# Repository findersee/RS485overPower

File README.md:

# RS485overPower

RS-485 Over DC Powerline adapter

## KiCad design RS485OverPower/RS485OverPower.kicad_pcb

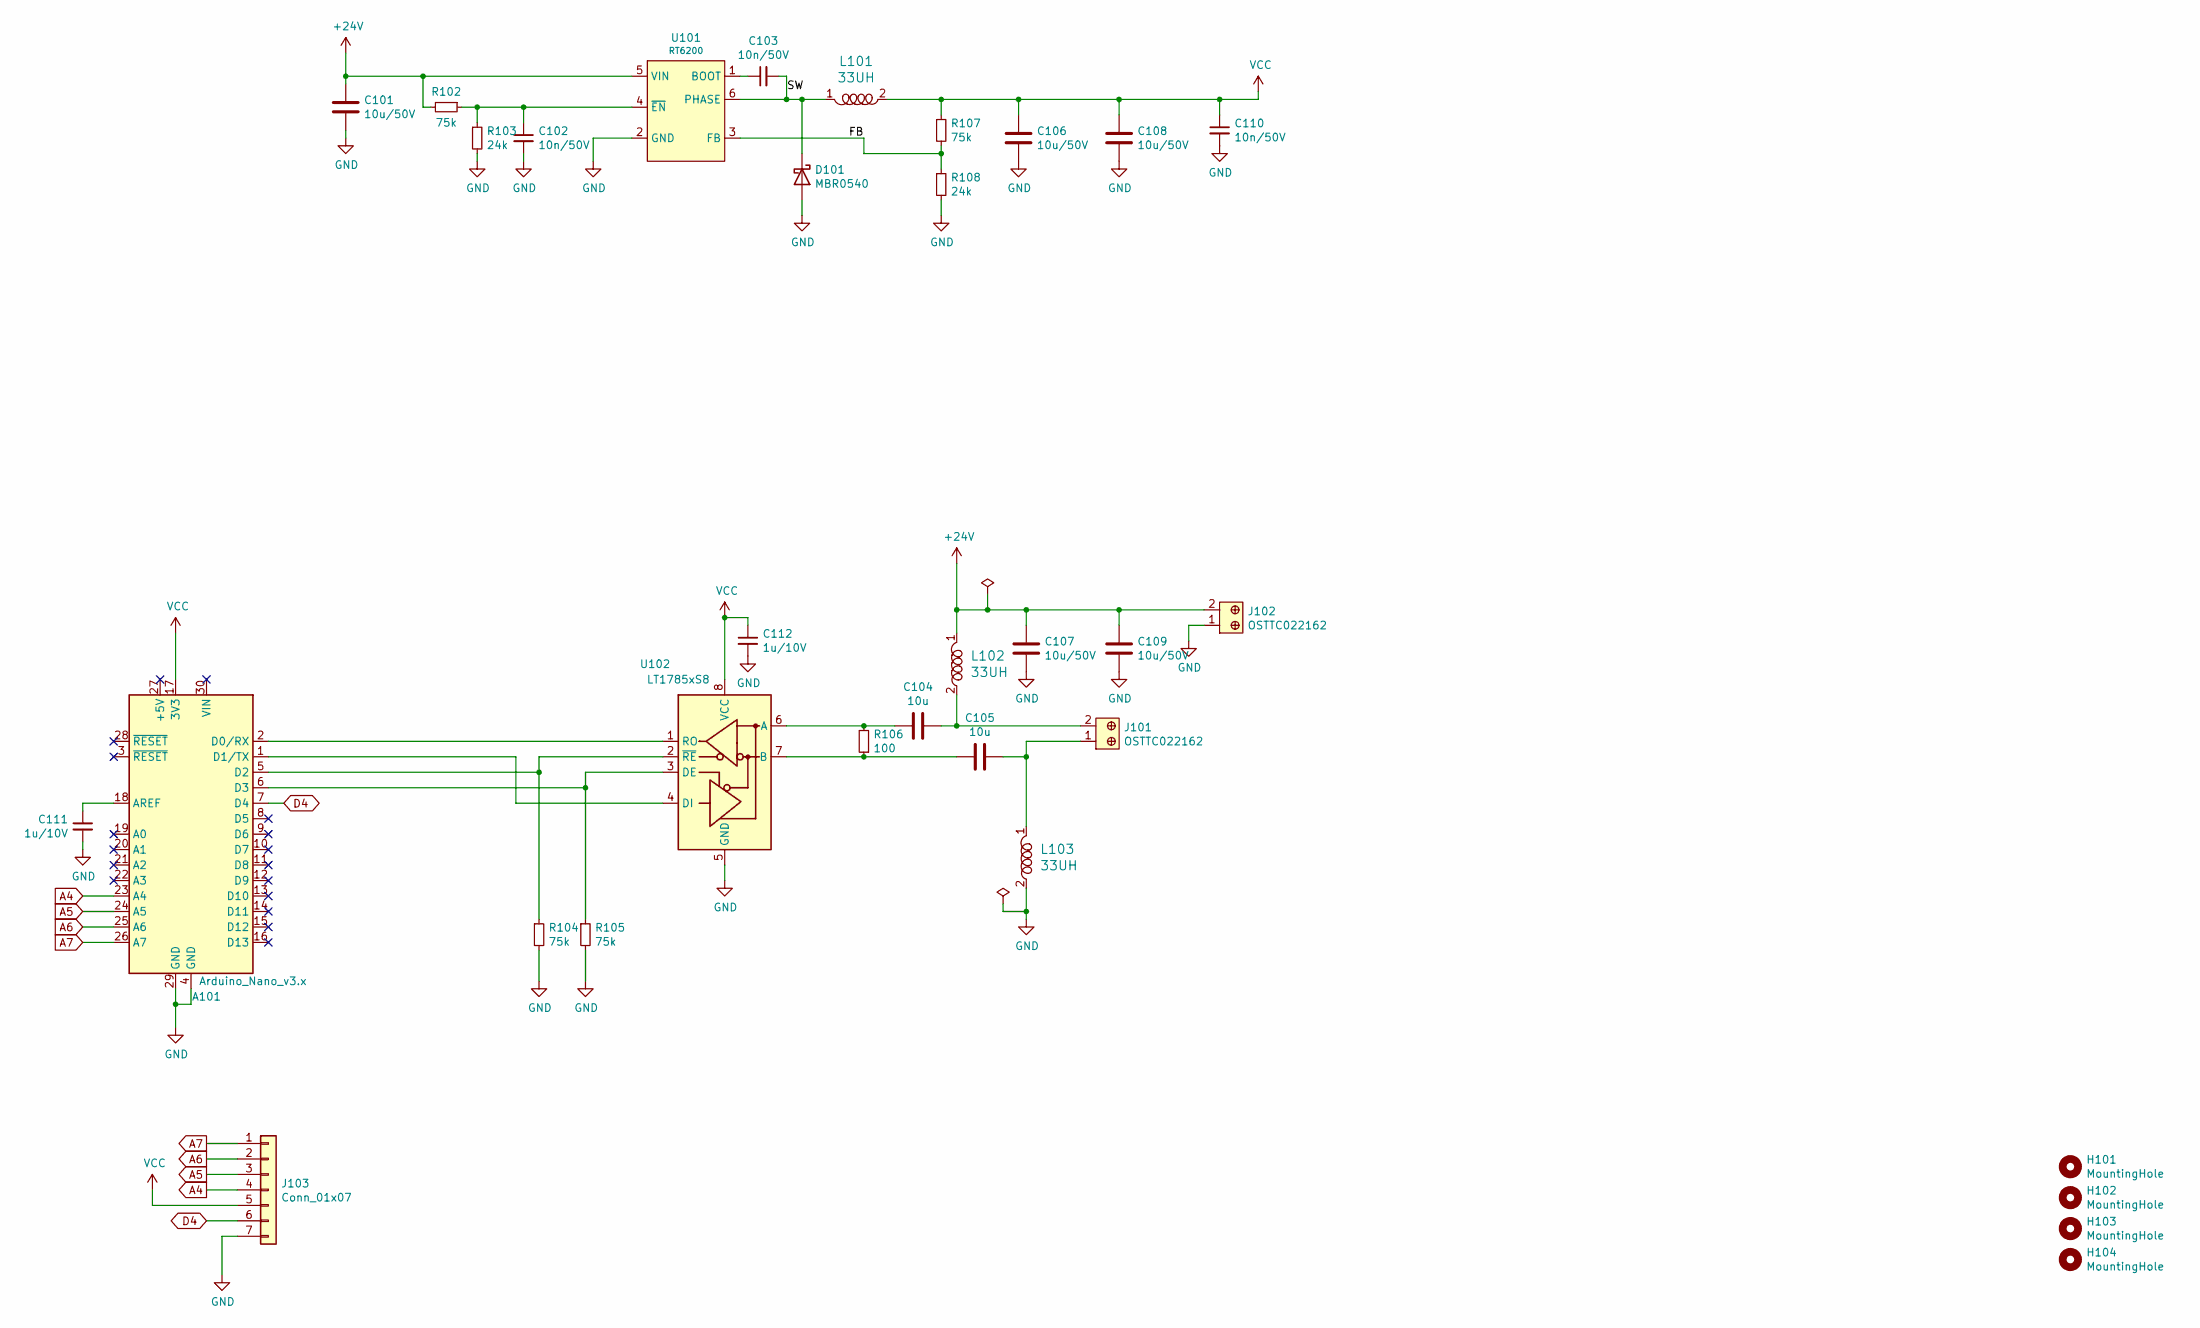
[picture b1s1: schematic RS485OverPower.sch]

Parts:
A101: Arduino_Nano_v3.x; Arduino_Nano
C101, C106, C107, C108: 10u/50V; C_0805_2012Metric
C102, C103, C110: 10n/50V; C_0603_1608Metric
C104, C105: 10u; C_0805_2012Metric
C109: 10u/50V; C_0603_1608Metric
C111, C112: 1u/10V; C_0603_1608Metric
D101: MBR0540; D_SOD-123
H101, H102, H103, H104: MountingHole; MountingHole_3.2mm_M3
J101, J102: OSTTC022162; Term_Block_1x2_P5.08MM; MPN OSTTC022162; Digi-Key_PN ED2609-ND
J103: Conn_01x07; PinHeader_1x07_P2.54mm_Vertical
L101, L102, L103: 33UH; MWSA0603; MPN MWSA0603-330MT; LCSC PN C132138
R102, R104, R105, R107: 75k; R_0603_1608Metric
R103, R108: 24k; R_0603_1608Metric
R106: 100; R_0603_1608Metric
U101: RT6200; SOT-23-6
U102: LT1785xS8; SOIC-8_3.9x4.9mm_P1.27mm

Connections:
+24V: C101.1, C107.1, C109.1, J102.2, L102.1, R102.2, U101.5 (VIN)
/FB: R107.2, R108.1, U101.3 (FB)
/SW: C103.2, D101.1 (K), L101.1, U101.6 (PHASE)
A4: A101.23 (A4), J103.4
A5: A101.24 (A5), J103.3
A6: A101.25 (A6), J103.2
A7: A101.26 (A7), J103.1
D4: A101.7 (D4), J103.6
GND: A101.4 (GND), A101.29 (GND), C101.2, C102.2, C106.2, C107.2, C108.2, C109.2, C110.2, C111.2, C112.2, D101.2 (A), J102.1, J103.7, L103.2, R103.2, R104.2, R105.2, R108.2, U101.2 (GND), U102.5 (GND)
unnamed: A101.1 (D1/TX), U102.4 (DI)
unnamed: A101.2 (D0/RX), U102.1 (RO)
unnamed: A101.5 (D2), R104.1, U102.2 (~RE)
unnamed: A101.6 (D3), R105.1, U102.3 (DE)
unnamed: A101.18 (AREF), C111.1
unnamed: C102.1, R102.1, R103.1, U101.4 (~EN)
unnamed: C103.1, U101.1 (BOOT)
unnamed: C104.1, J101.2, L102.2
unnamed: C104.2, R106.2, U102.6 (A)
unnamed: C105.1, R106.1, U102.7 (B)
unnamed: C105.2, J101.1, L103.1
VCC: A101.17 (3V3), C106.1, C108.1, C110.1, C112.1, J103.5, L101.2, R107.1, U102.8 (VCC)

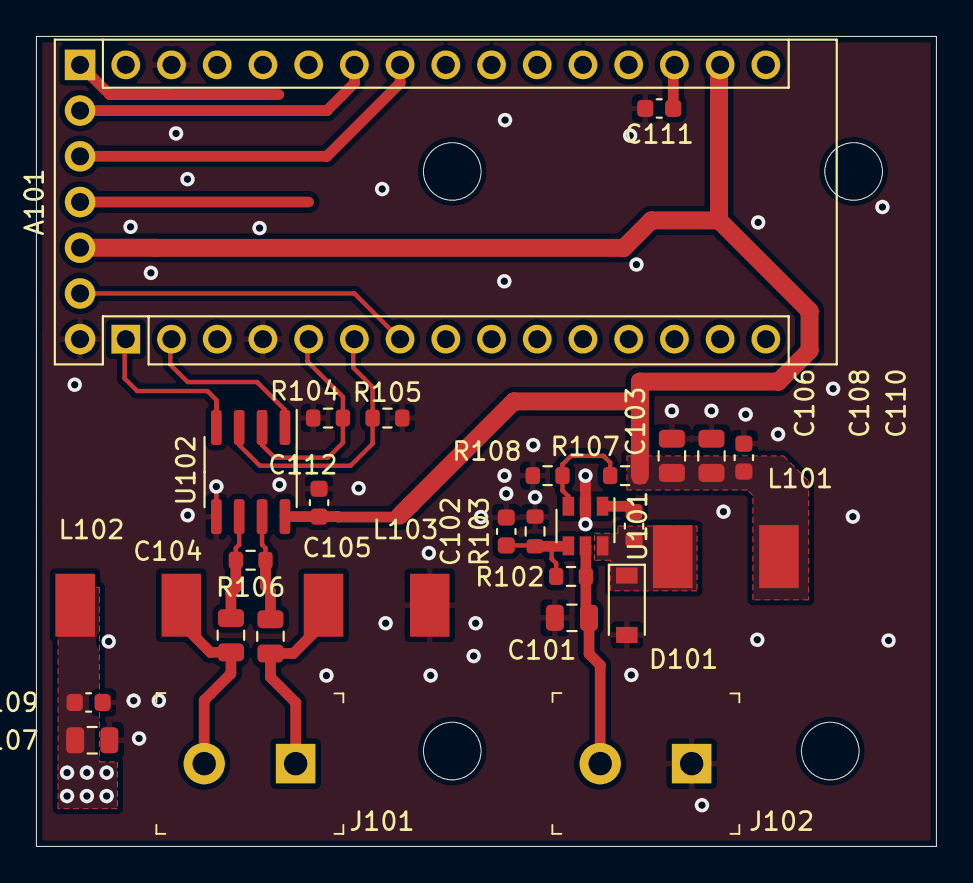
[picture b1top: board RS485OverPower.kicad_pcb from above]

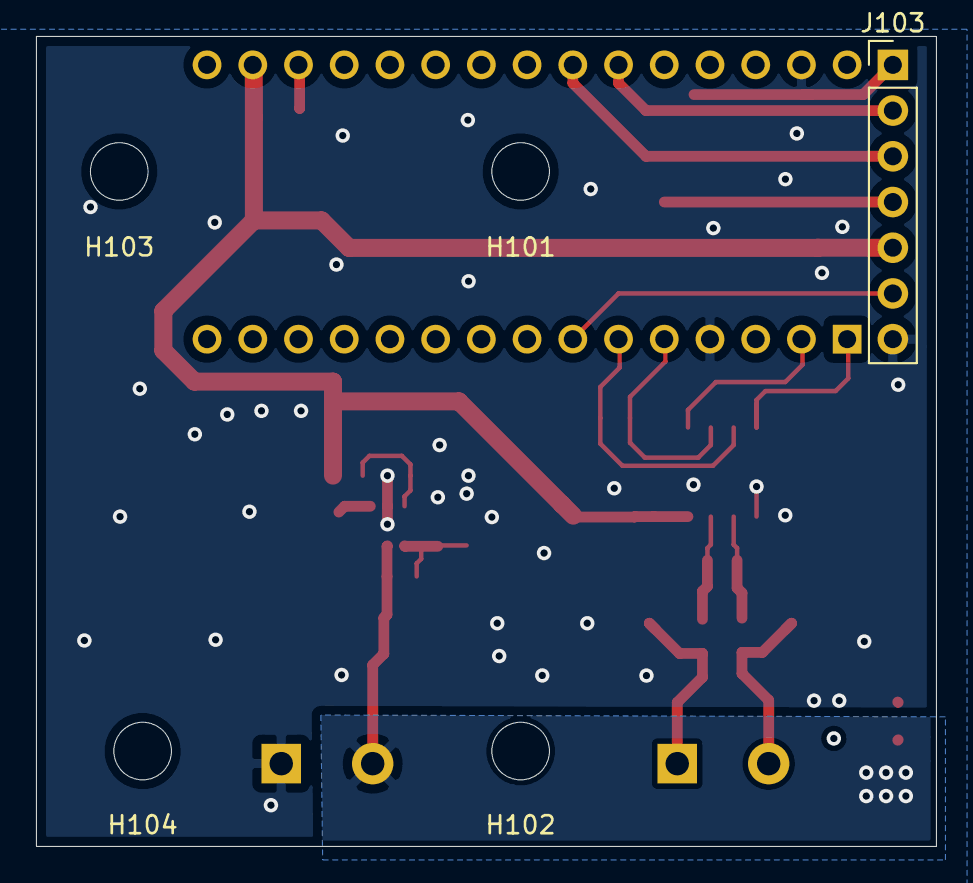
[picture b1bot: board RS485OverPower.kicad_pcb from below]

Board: 2 copper layers, 50.0 x 45.0 mm, 33 parts (5 on the bottom side), 21 nets.

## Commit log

2021-01-30 First layout done
2021-01-30 Next commit
2021-01-30 Bom update
2021-01-30 Removed BOM config
2021-01-30 Added connector for I/O
2021-01-30 Layout improvements
2021-01-30 Added schematic PDF and 3D picture
